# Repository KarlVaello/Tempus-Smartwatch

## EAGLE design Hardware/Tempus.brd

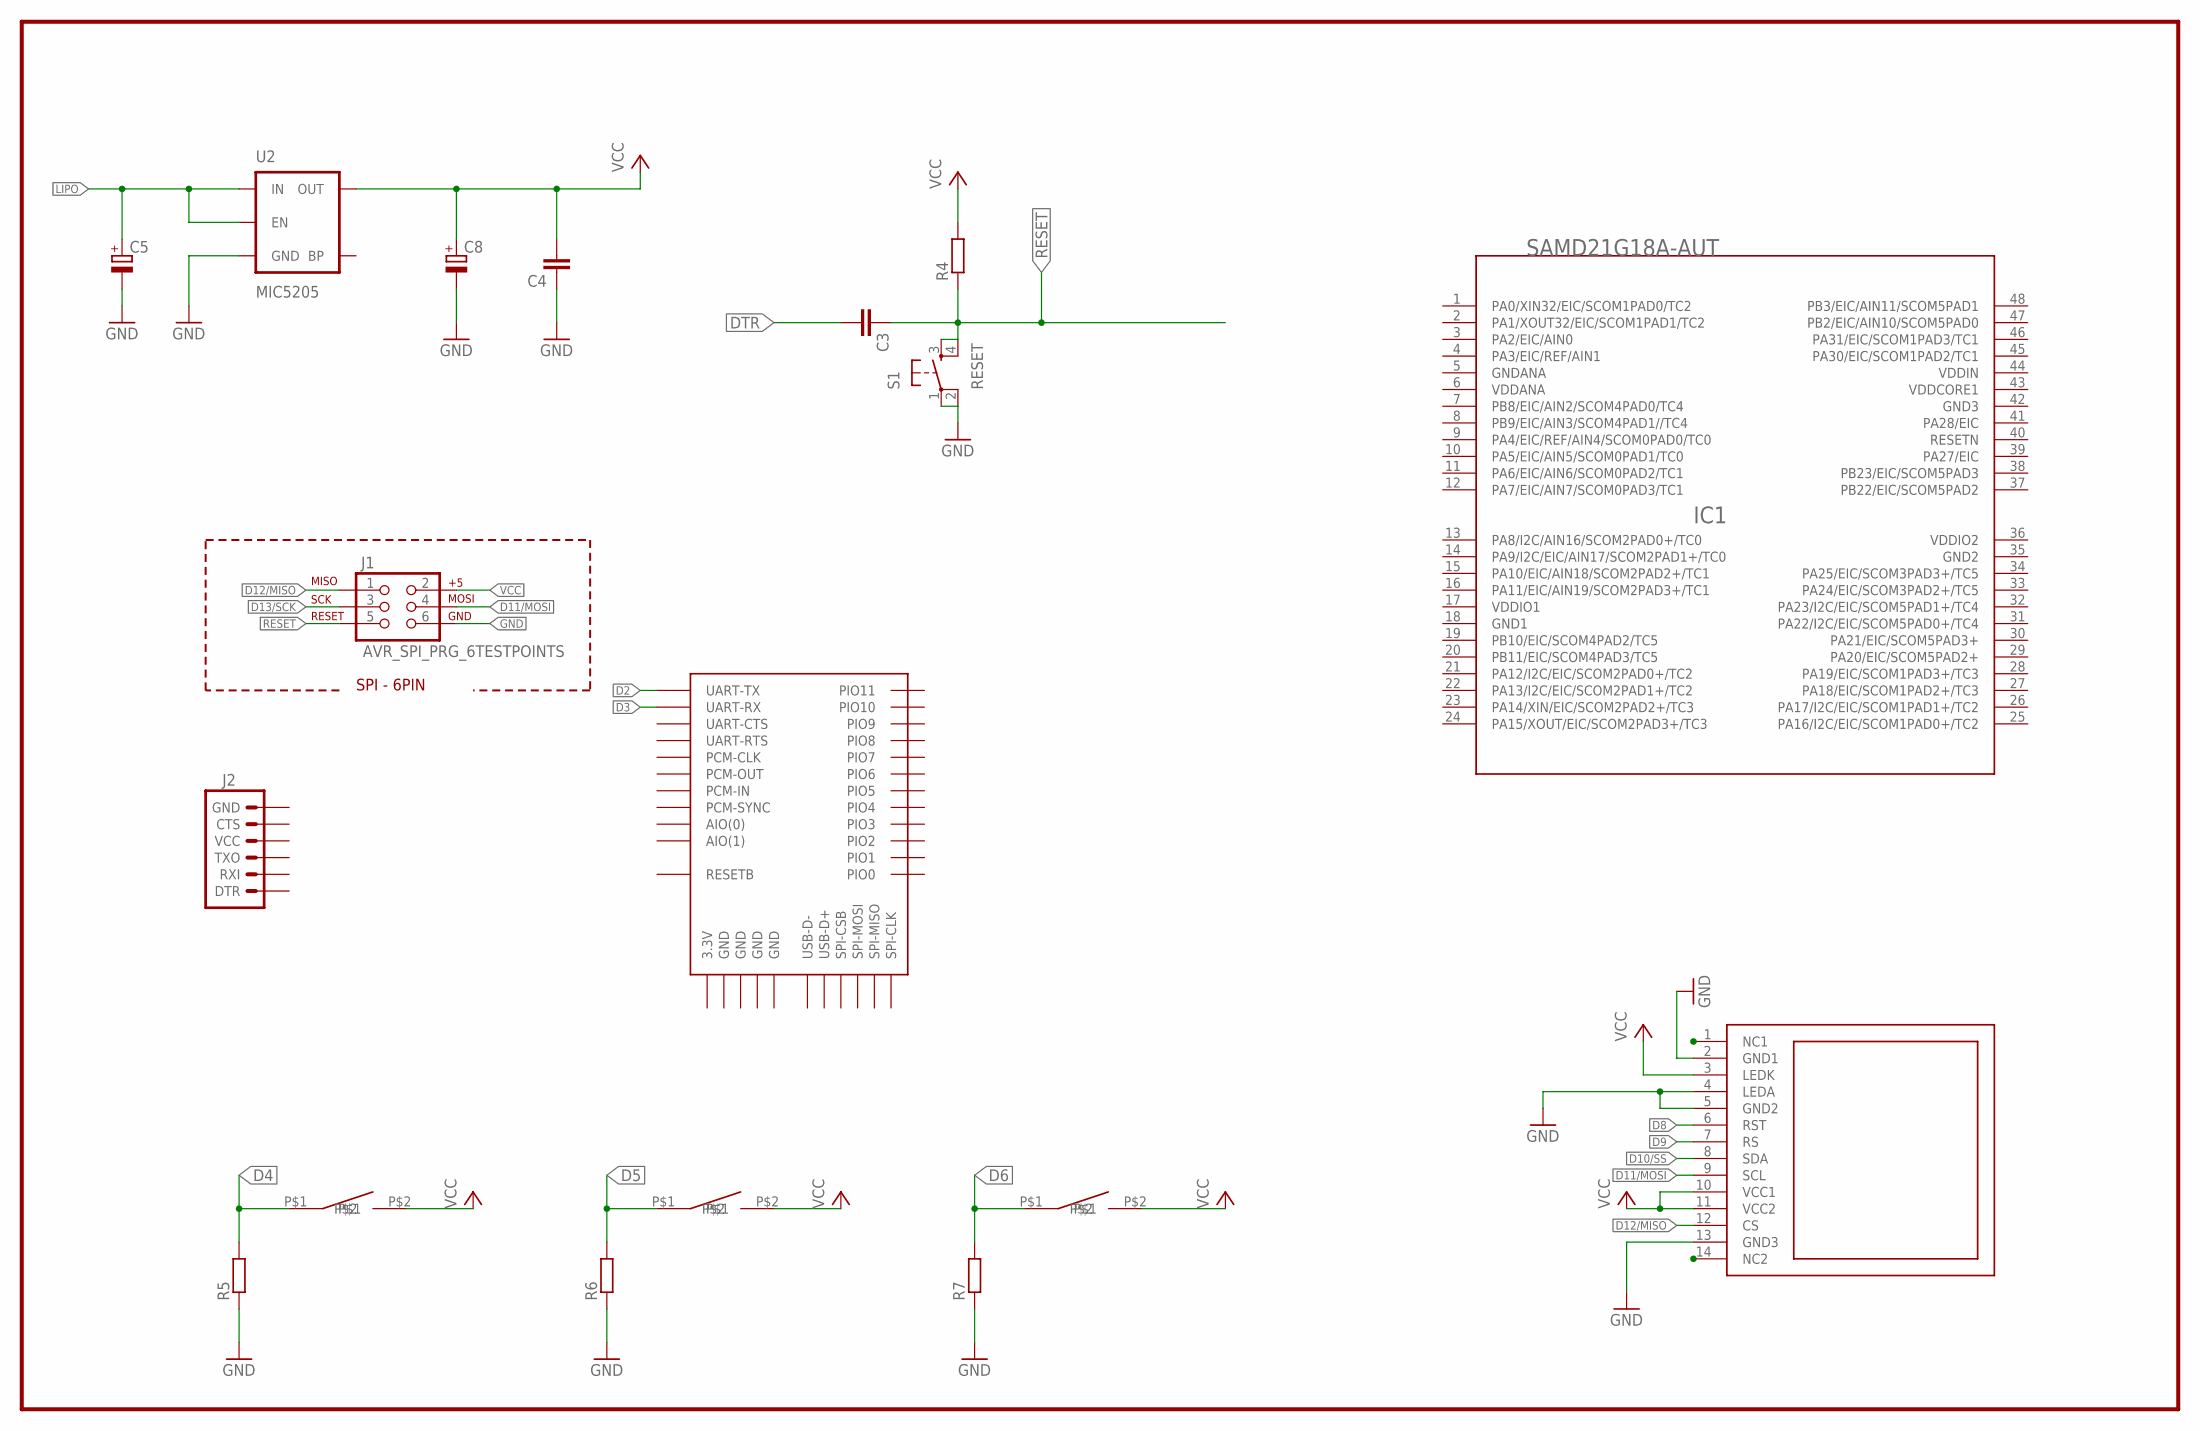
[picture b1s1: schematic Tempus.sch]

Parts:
C3, C4: C-EUC1608; C1608
C5, C8: CPOL-EUA/3216-18R; A/3216-18R
IC1: SAMD21G18A-AUT; TQFP48-7X7
J1: AVR_SPI_PRG_6TESTPOINTS; 2X3_TEST_POINTS
J2: ARDUINO_SERIAL_PROGRAMPTH; 1X06
R4, R5, R6, R7: R-EU_R0603; R0603
S1: RESET; TACTILE-SWITCH-SMD
U2: MIC5205; SOT23-5
U$1: DISP_TFT18; TFT18
U$2, U$3, U$4: MICRO_SIDE_TACT_BUTTON_SMD_SECURE
U$5: BTM400_6B

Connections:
3.3V: U$5.3.3V
D2: U$5.UART-TX
D3: U$5.UART-RX
D4: R5.2, U$4.P$1
D5: R6.2, U$2.P$1
D6: R7.2, U$3.P$1
D8: U$1.6 (RST)
D9: U$1.7 (RS)
D10/SS: U$1.8 (SDA)
D11/MOSI: J1.4, U$1.9 (SCL)
D12/MISO: J1.1, U$1.12 (CS)
D13/SCK: J1.3
DTR: C3.2
GND: C4.1, C5.-, C8.-, J1.6, R5.1, R6.1, R7.1, S1.1, S1.2, U2.2 (GND), U$1.2 (GND1), U$1.4 (LEDA), U$1.5 (GND2), U$1.13 (GND3), U$5.GND@1 (GND), U$5.GND@2 (GND), U$5.GND@3 (GND), U$5.GND@4 (GND)
GND1: IC1.18 (GND1)
GND2: IC1.35 (GND2)
GND3: IC1.42 (GND3)
GNDANA: IC1.5 (GNDANA)
LIPO: C5.+, U2.1 (IN), U2.3 (EN)
RESET: C3.1, J1.5, R4.1, S1.3, S1.4
VCC: C4.2, C8.+, J1.2, R4.2, U2.5 (OUT), U$1.3 (LEDK), U$1.10 (VCC1), U$1.11 (VCC2), U$2.P$2, U$3.P$2, U$4.P$2
VDDANA: IC1.6 (VDDANA)
VDDIN: IC1.44 (VDDIN)
VDDIO1: IC1.17 (VDDIO1)
VDDIO2: IC1.36 (VDDIO2)

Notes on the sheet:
SPI - 6PIN

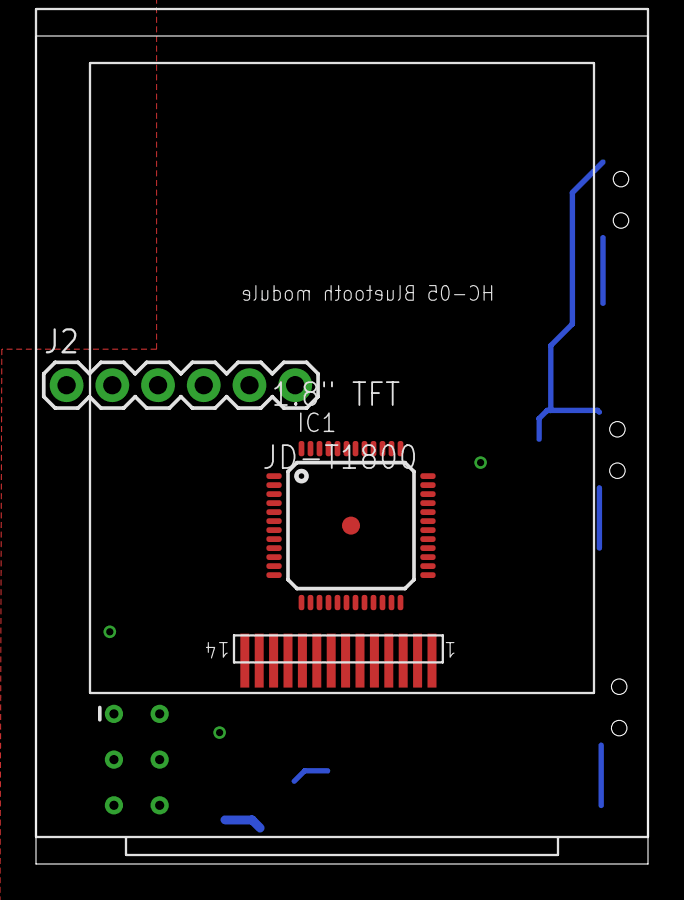
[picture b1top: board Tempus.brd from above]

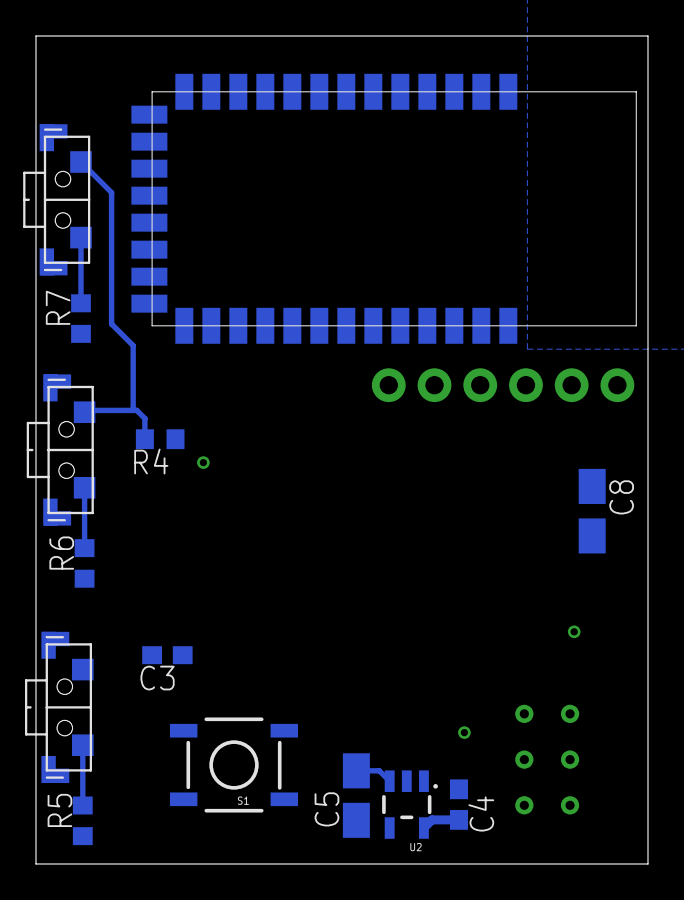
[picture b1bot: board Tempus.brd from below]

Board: 2 copper layers, 34.0 x 46.0 mm, 18 parts (14 on the bottom side), 9 nets.

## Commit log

2016-10-03 Initial commit
    Initial commit
2016-10-03 Hardware modifications
    Hardware modifications
2016-10-05 Hardware
    Hardware
2016-10-05 Deleted local EagleCad libraries
    Deleted local EagleCad libraries
2016-10-09 Hardware modifications
    Hardware modifications. Tempus now based on ARM 32-bit, 3.3V at 48Mhz
2016-10-11 Added Project description
    Added Project description

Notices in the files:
parts and their libraries:
SparkFun-Retired: Licensing:Creative Commons ShareAlike 4.0 International - https://creativecommons.org/licenses/by-sa/4.0
